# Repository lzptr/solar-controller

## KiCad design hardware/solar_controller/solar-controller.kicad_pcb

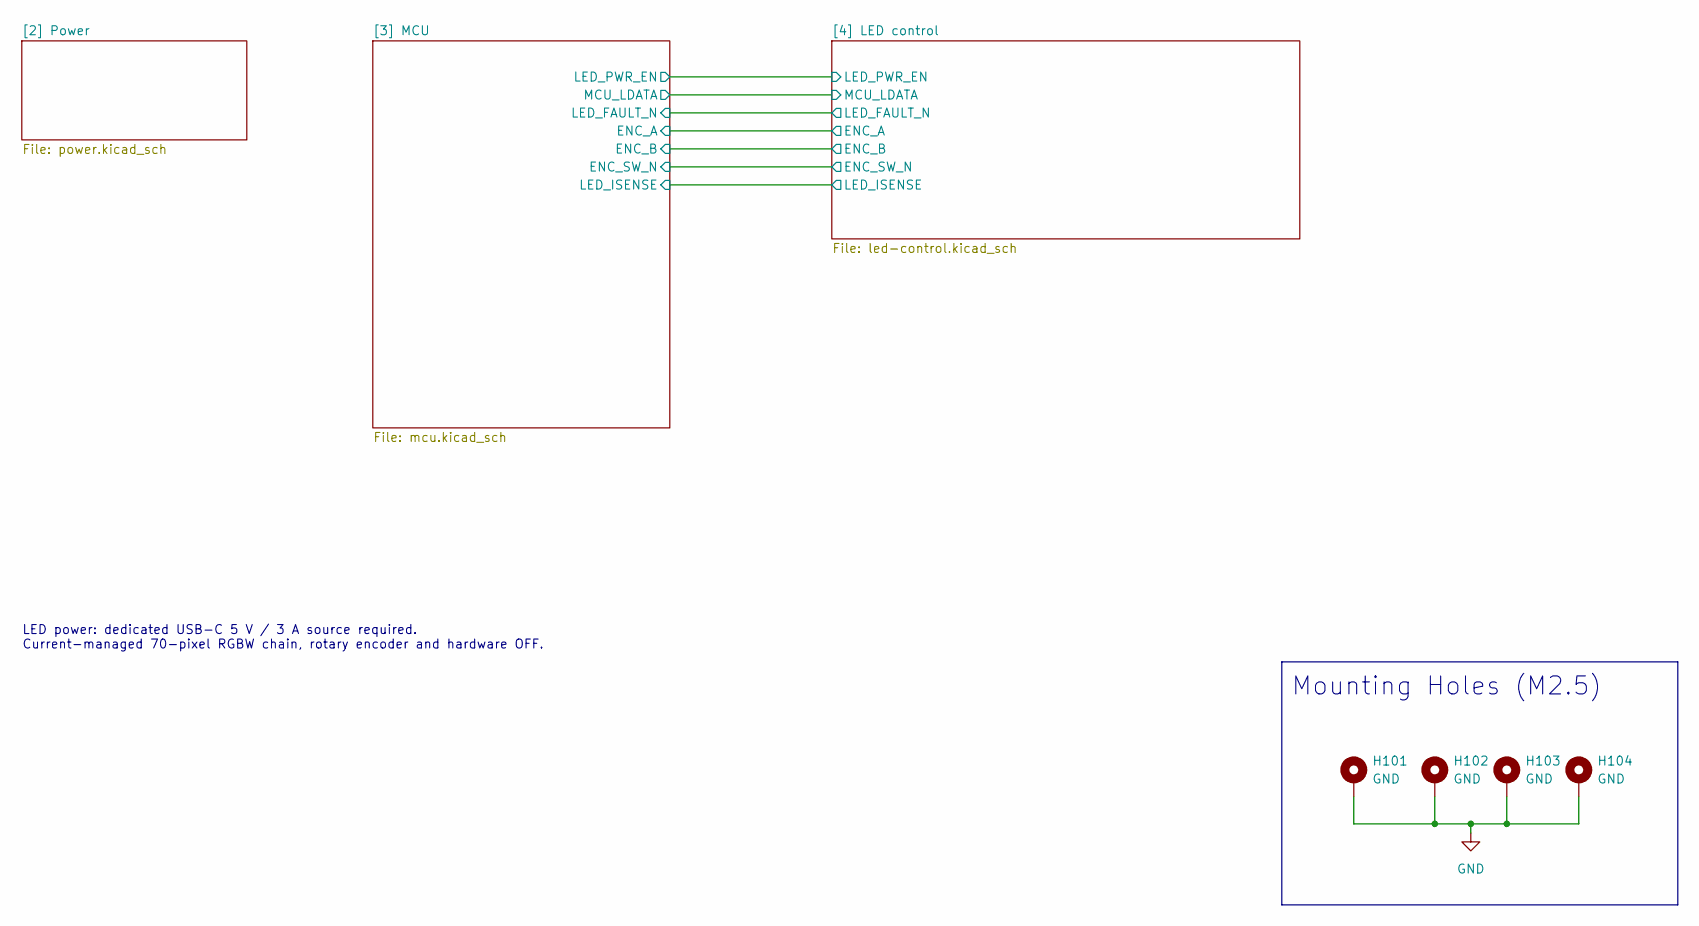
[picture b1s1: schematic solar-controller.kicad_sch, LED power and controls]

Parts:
H101, H102, H103, H104: GND; MountingHole_2.7mm_M2.5_ISO14580_Pad

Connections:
GND: H101.1 (1_1), H102.1 (1_1), H103.1 (1_1), H104.1 (1_1); also elsewhere on the board

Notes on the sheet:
Mounting Holes (M2.5)
LED power: dedicated USB-C 5 V / 3 A source required. Current-managed 70-pixel RGBW chain, rotary encoder and hardware OFF.

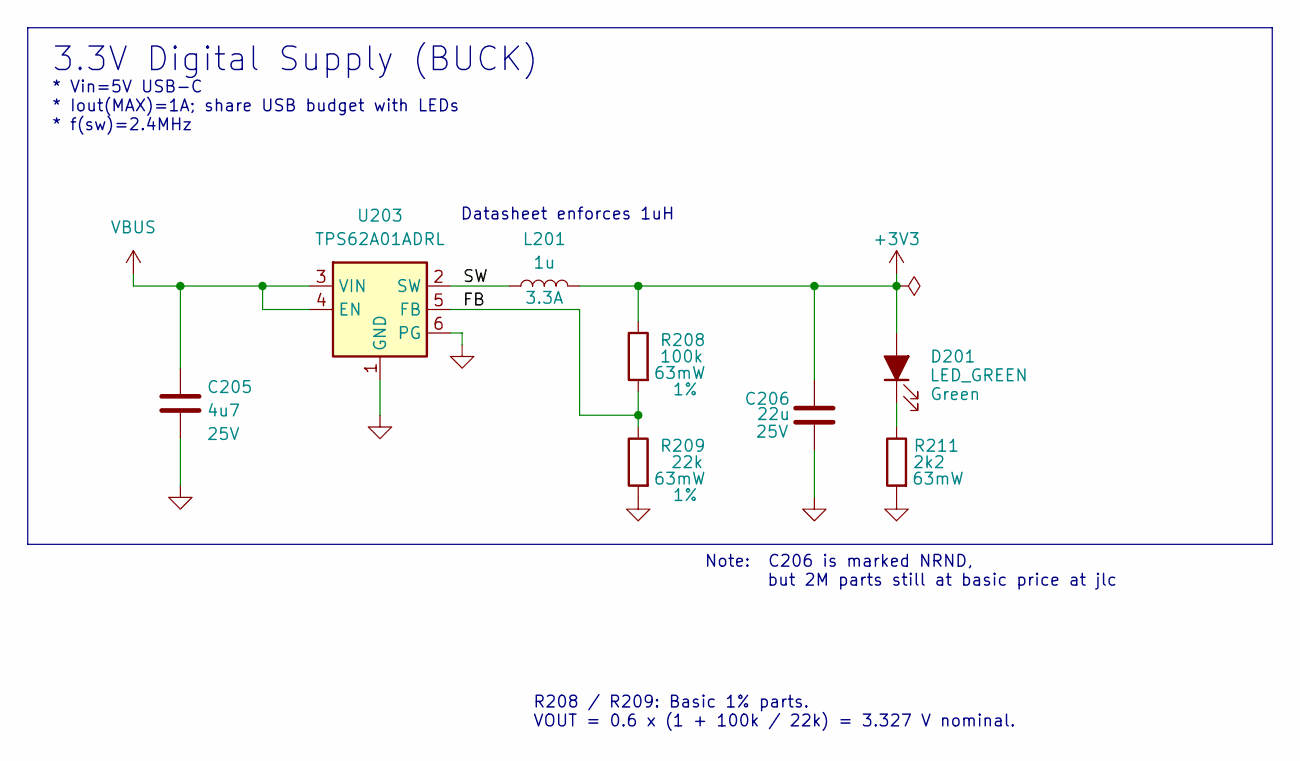
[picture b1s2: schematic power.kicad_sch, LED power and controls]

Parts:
C205: 4u7; C_0805_2012Metric; Rating 25V; LCSC Part # C1779
C206: 22u; C_0805_2012Metric; Rating 25V; LCSC Part # C45783
D201: LED_GREEN; LED_0603_1608Metric; Rating Green; LCSC Part # C965804
L201: 1u; L_1008_2520Metric; Rating 3.3A; LCSC Part # C435392
R208: 100k; R_0402_1005Metric; Rating 63mW; LCSC Part # C25741
R209: 22k; R_0402_1005Metric; Rating 63mW; LCSC Part # C25768
R211: 2k2; R_0402_1005Metric; Rating 63mW; LCSC Part # C25879
U203: TPS62A01ADRL; SOT-563; LCSC Part # C5181455

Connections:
+3V3: C206.1, D201.2 (A), L201.2, R208.1; also elsewhere on the board
/[2] Power/FB: R208.2, R209.1, U203.5 (FB)
/[2] Power/SW: L201.1, U203.2 (SW)
GND: C205.2, C206.2, R209.2, R211.2, U203.1 (GND), U203.6 (PG); also elsewhere on the board
unnamed: D201.1 (K), R211.1
VBUS: C205.1, U203.3 (VIN), U203.4 (EN); also elsewhere on the board

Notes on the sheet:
* Vin=5V USB-C * Iout(MAX)=1A; share USB budget with LEDs * f(sw)=2.4MHz
Datasheet enforces 1uH
Note: C206 is marked NRND, but 2M parts still at basic price at jlc
3.3V Digital Supply (BUCK)
R208 / R209: Basic 1% parts. VOUT = 0.6 x (1 + 100k / 22k) = 3.327 V nominal.

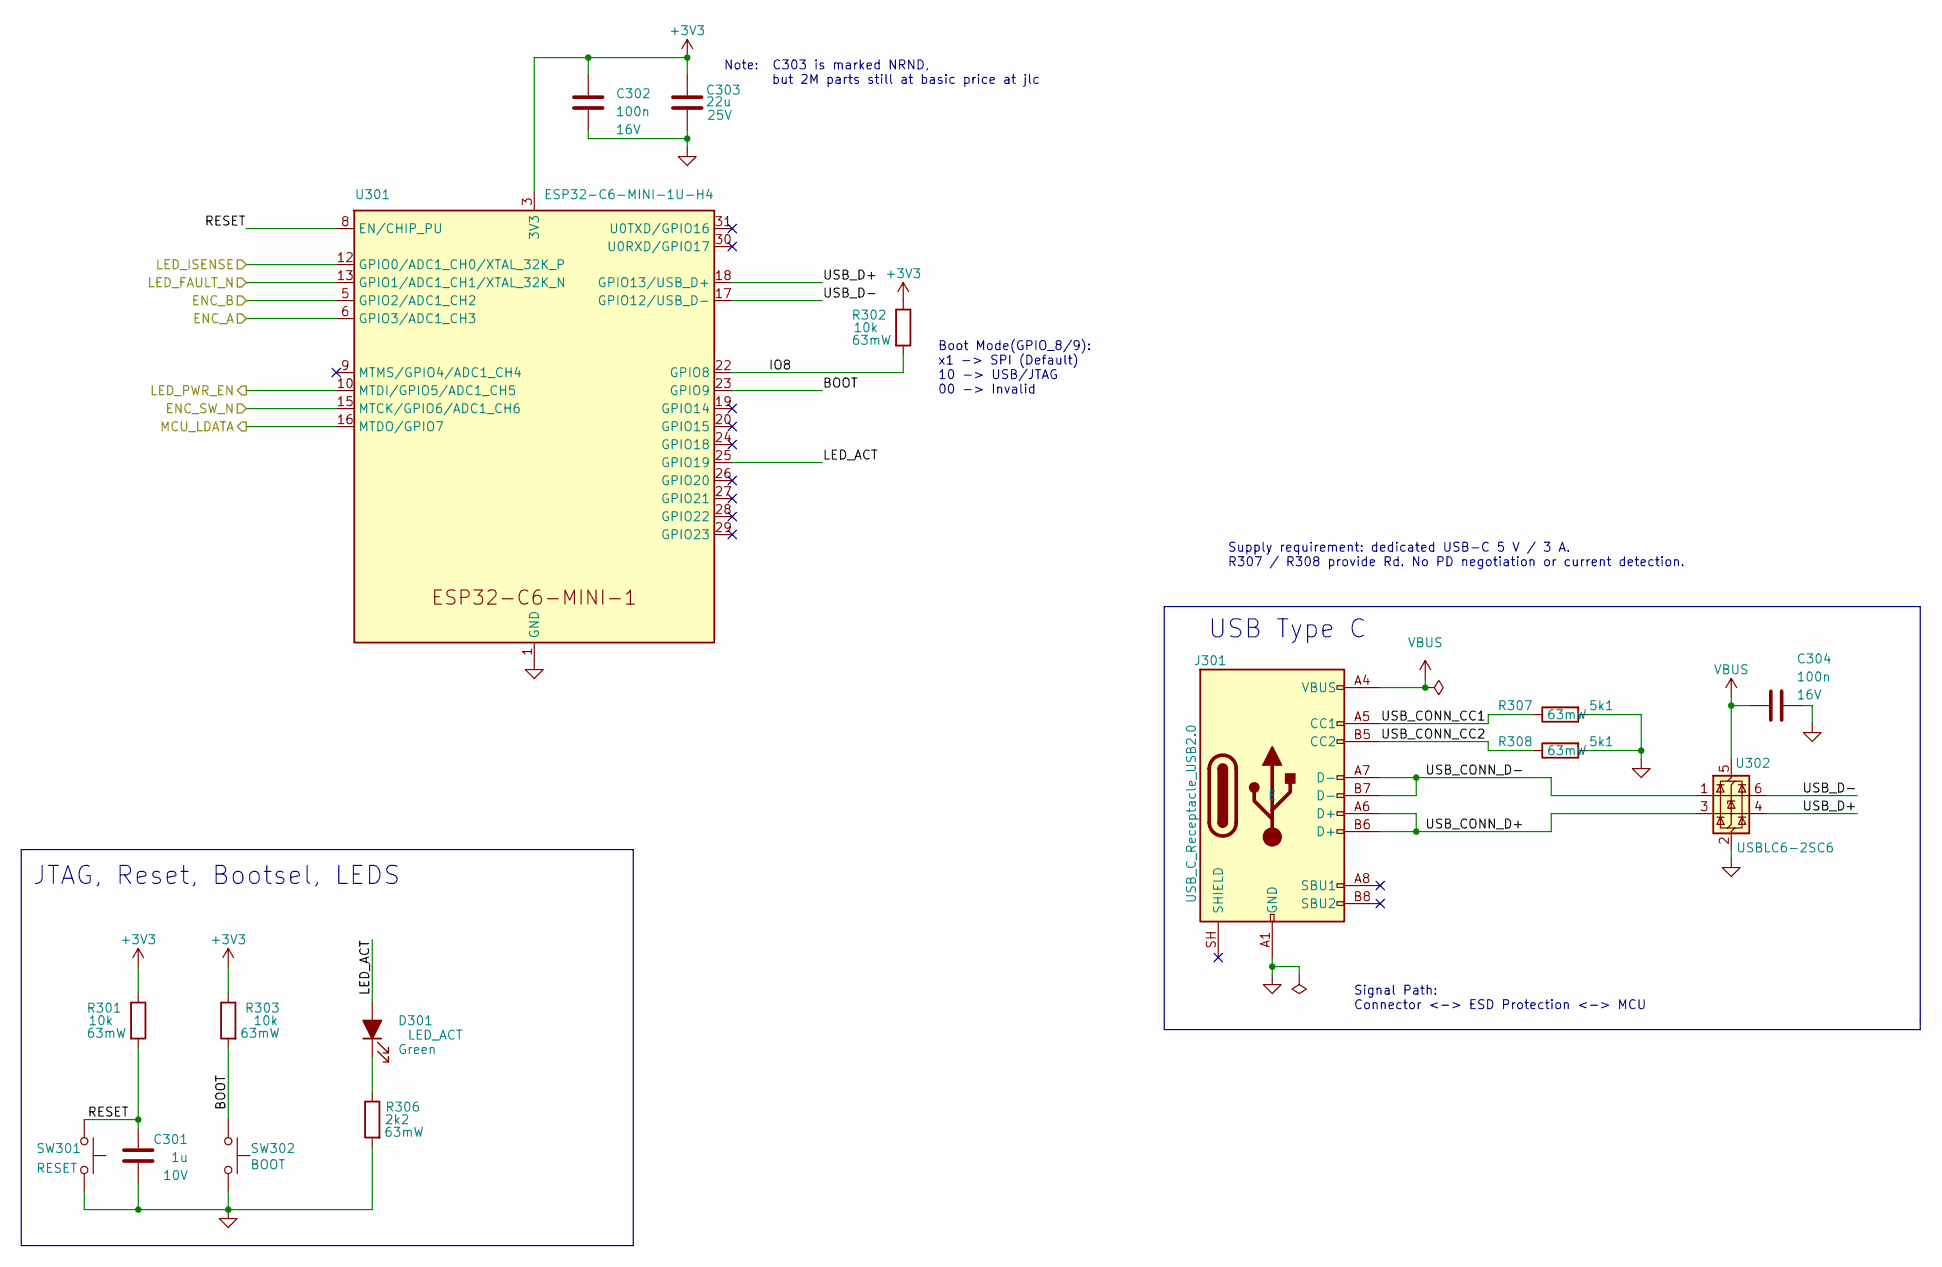
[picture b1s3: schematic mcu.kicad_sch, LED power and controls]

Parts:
C301: 1u; C_0402_1005Metric; Rating 10V; LCSC Part # C14445
C302, C304: 100n; C_0402_1005Metric; Rating 16V; LCSC Part # C1525
C303: 22u; C_0805_2012Metric; Rating 25V; LCSC Part # C45783
D301: LED_ACT; LED_0603_1608Metric; Rating Green; LCSC Part # C965804
J301: USB_C_Receptacle_USB2.0; USB_C_Receptacle_HRO_TYPE-C-31-M-12; LCSC Part # C165948
R301, R302, R303: 10k; R_0402_1005Metric; Rating 63mW; LCSC Part # C25744
R306: 2k2; R_0402_1005Metric; Rating 63mW; LCSC Part # C25879
R307, R308: 5k1; R_0402_1005Metric; Rating 63mW; LCSC Part # C25905
SW301: RESET; SW_SPST_TS-1088-xR020; LCSC Part # C720477
SW302: BOOT; SW_SPST_TS-1088-xR020; LCSC Part # C720477
U301: ESP32-C6-MINI-1U-H4; ESP32-C6-MINI-1U; LCSC Part # C20627095
U302: USBLC6-2SC6; SOT-23-6; LCSC Part # C5261088

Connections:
+3V3: C302.1, C303.1, R301.1, R302.1, R303.1, U301.3 (3V3); also elsewhere on the board
/[3] MCU/BOOT: R303.2, SW302.1, U301.23 (GPIO9)
/[3] MCU/ENC_A: U301.6 (GPIO3/ADC1_CH3); also elsewhere on the board
/[3] MCU/ENC_B: U301.5 (GPIO2/ADC1_CH2); also elsewhere on the board
/[3] MCU/ENC_SW_N: U301.15 (MTCK/GPIO6/ADC1_CH6); also elsewhere on the board
/[3] MCU/IO8: R302.2, U301.22 (GPIO8)
/[3] MCU/LED_ACT: D301.2 (A), U301.25 (GPIO19)
/[3] MCU/LED_FAULT_N: U301.13 (GPIO1/ADC1_CH1/XTAL_32K_N); also elsewhere on the board
/[3] MCU/LED_ISENSE: U301.12 (GPIO0/ADC1_CH0/XTAL_32K_P); also elsewhere on the board
/[3] MCU/LED_PWR_EN: U301.10 (MTDI/GPIO5/ADC1_CH5); also elsewhere on the board
/[3] MCU/MCU_LDATA: U301.16 (MTDO/GPIO7); also elsewhere on the board
/[3] MCU/RESET: C301.1, R301.2, SW301.1, U301.8 (EN/CHIP_PU)
/[3] MCU/USB_CONN_CC1: J301.A5 (CC1), R307.1
/[3] MCU/USB_CONN_CC2: J301.B5 (CC2), R308.1
/[3] MCU/USB_CONN_D+: J301.A6 (D+), J301.B6 (D+), U302.3 (I/O2)
/[3] MCU/USB_CONN_D-: J301.A7 (D-), J301.B7 (D-), U302.1 (I/O1)
/[3] MCU/USB_D+: U301.18 (GPIO13/USB_D+), U302.4 (I/O2)
/[3] MCU/USB_D-: U301.17 (GPIO12/USB_D-), U302.6 (I/O1)
GND: C301.2, C302.2, C303.2, C304.2, J301.A1 (GND), J301.A12 (GND), J301.B1 (GND), J301.B12 (GND), R306.2, R307.2, R308.2, SW301.2, SW302.2, U301.1 (GND), U301.2 (GND), U301.11 (GND), U301.14 (GND), U301.36 (GND), U301.37 (GND), U301.38 (GND), U301.39 (GND), U301.40 (GND), U301.41 (GND), U301.42 (GND), U301.43 (GND), U301.44 (GND), U301.45 (GND), U301.46 (GND), U301.47 (GND), U301.48 (GND), U301.49 (GND), U301.50 (GND), U301.51 (GND), U301.52 (GND), U301.53 (GND), U302.2 (GND); also elsewhere on the board
unnamed: D301.1 (K), R306.1
VBUS: C304.1, J301.A4 (VBUS), J301.A9 (VBUS), J301.B4 (VBUS), J301.B9 (VBUS), U302.5 (VBUS); also elsewhere on the board

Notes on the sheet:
Signal Path: Connector <-> ESD Protection <-> MCU
Note: C303 is marked NRND, but 2M parts still at basic price at jlc
Boot Mode(GPIO_8/9): x1 -> SPI (Default) 10 -> USB/JTAG 00 -> Invalid
USB Type C
Supply requirement: dedicated USB-C 5 V / 3 A. R307 / R308 provide Rd. No PD negotiation or current detection.
JTAG, Reset, Bootsel, LEDS

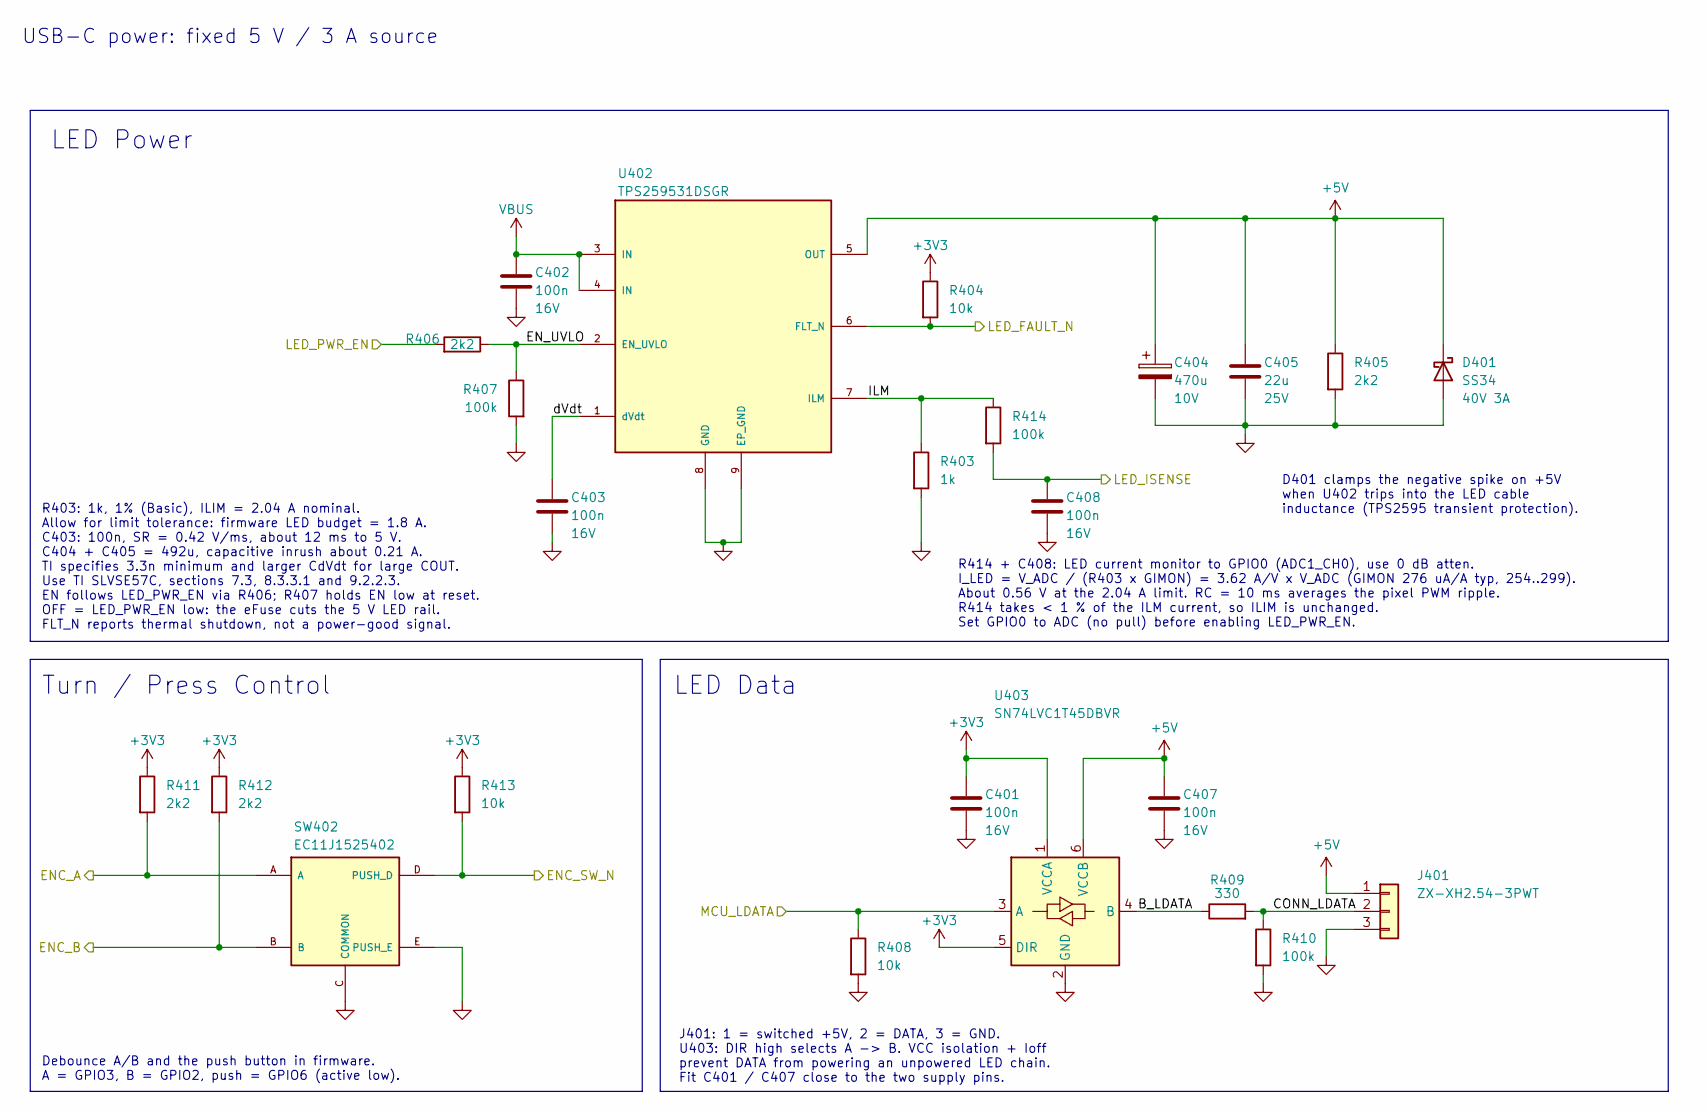
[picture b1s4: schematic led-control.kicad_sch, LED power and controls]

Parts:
C401, C402, C403, C407, C408: 100n; C_0402_1005Metric; Rating 16V; LCSC Part # C1525
C404: 470u; CP_Elec_6.3x7.7; Rating 10V; MPN MA10V470M6X8; LCSC Part # C46550459
C405: 22u; C_0805_2012Metric; Rating 25V; LCSC Part # C45783
D401: SS34; D_SMA; Rating 40V 3A; MPN SS34; LCSC Part # C8678
J401: ZX-XH2.54-3PWT; Megastar_ZX-XH2.54-3PWT; Rating 3A / contact; MPN ZX-XH2.54-3PWT; LCSC Part # C7429672
R403: 1k; R_0402_1005Metric; Rating 62.5mW; MPN 0402WGF1001TCE; LCSC Part # C11702
R404, R408, R413: 10k; R_0402_1005Metric; Rating 63mW; LCSC Part # C25744
R405, R406, R411, R412: 2k2; R_0402_1005Metric; Rating 63mW; LCSC Part # C25879
R407, R410, R414: 100k; R_0402_1005Metric; Rating 63mW; LCSC Part # C25741
R409: 330; R_0402_1005Metric; Rating 63mW; LCSC Part # C25104
SW402: EC11J1525402; ALPS_EC11J1525402; Rating 10mA / 5V; LCSC Part # C209762
U402: TPS259531DSGR; Texas_DSG0008A_WSON-8-1EP_2x2mm_P0.5mm_EP0.9x1.6mm; Rating 5V branch / 2.04A nominal; LCSC Part # C2155674
U403: SN74LVC1T45DBVR; SOT-23-6; Rating 3.3V -> switched 5V; LCSC Part # C7843

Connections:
+3V3: C401.1, R404.1, R411.1, R412.1, R413.1, U403.1 (VCCA), U403.5 (DIR); also elsewhere on the board
+5V: C404.1, C405.1, C407.1, D401.1 (K), J401.1, R405.1, U402.5 (OUT), U403.6 (VCCB)
/[3] MCU/ENC_A: R411.2, SW402.A; also elsewhere on the board
/[3] MCU/ENC_B: R412.2, SW402.B; also elsewhere on the board
/[3] MCU/ENC_SW_N: R413.2, SW402.D (PUSH_D); also elsewhere on the board
/[3] MCU/LED_FAULT_N: R404.2, U402.6 (FLT_N); also elsewhere on the board
/[3] MCU/LED_ISENSE: C408.1, R414.2; also elsewhere on the board
/[3] MCU/LED_PWR_EN: R406.2; also elsewhere on the board
/[3] MCU/MCU_LDATA: R408.1, U403.3 (A); also elsewhere on the board
/[4] LED control/B_LDATA: R409.1, U403.4 (B)
/[4] LED control/CONN_LDATA: J401.2, R409.2, R410.1
/[4] LED control/EN_UVLO: R406.1, R407.1, U402.2 (EN_UVLO)
/[4] LED control/ILM: R403.1, R414.1, U402.7 (ILM)
/[4] LED control/dVdt: C403.1, U402.1 (dVdt)
GND: C401.2, C402.2, C403.2, C404.2, C405.2, C407.2, C408.2, D401.2 (A), J401.3, R403.2, R405.2, R407.2, R408.2, R410.2, SW402.C (COMMON), SW402.E (PUSH_E), U402.8 (GND), U402.9 (EP_GND), U403.2 (GND); also elsewhere on the board
VBUS: C402.1, U402.3 (IN), U402.4 (IN); also elsewhere on the board

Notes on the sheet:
USB-C power: fixed 5 V / 3 A source
LED Data
R403: 1k, 1% (Basic), ILIM = 2.04 A nominal. Allow for limit tolerance: firmware LED budget = 1.8 A. C403: 100n, SR = 0.42 V/ms, about 12 ms to 5 V. C404 + C405 = 492u, capacitive inrush about 0.21 A. TI specifies 3.3n minimum and larger CdVdt for large COUT. Use TI SLVSE57C, sections 7.3, 8.3.3.1 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
LED Power
J401: 1 = switched +5V, 2 = DATA, 3 = GND. U403: DIR high selects A -> B. VCC isolation + Ioff prevent DATA from powering an unpowered LED chain. Fit C401 / C407 close to the two supply pins.
Turn / Press Control
R414 + C408: LED current monitor to GPIO0 (ADC1_CH0), use 0 dB atten. I_LED = V_ADC / (R403 x GIMON) = 3.62 A/V x V_ADC (GIMON 276 uA/A typ, 254..299). About 0.56 V at the 2.04 A limit. RC = 10 ms averages the pixel PWM ripple. R414 takes < 1 % of the ILM current, so ILIM is unchanged. Set GPIO0 to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
D401 clamps the negative spike on +5V when U402 trips into the LED cable inductance (TPS2595 transient protection).
Debounce A/B and the push button in firmware. A = GPIO3, B = GPIO2, push = GPIO6 (active low).

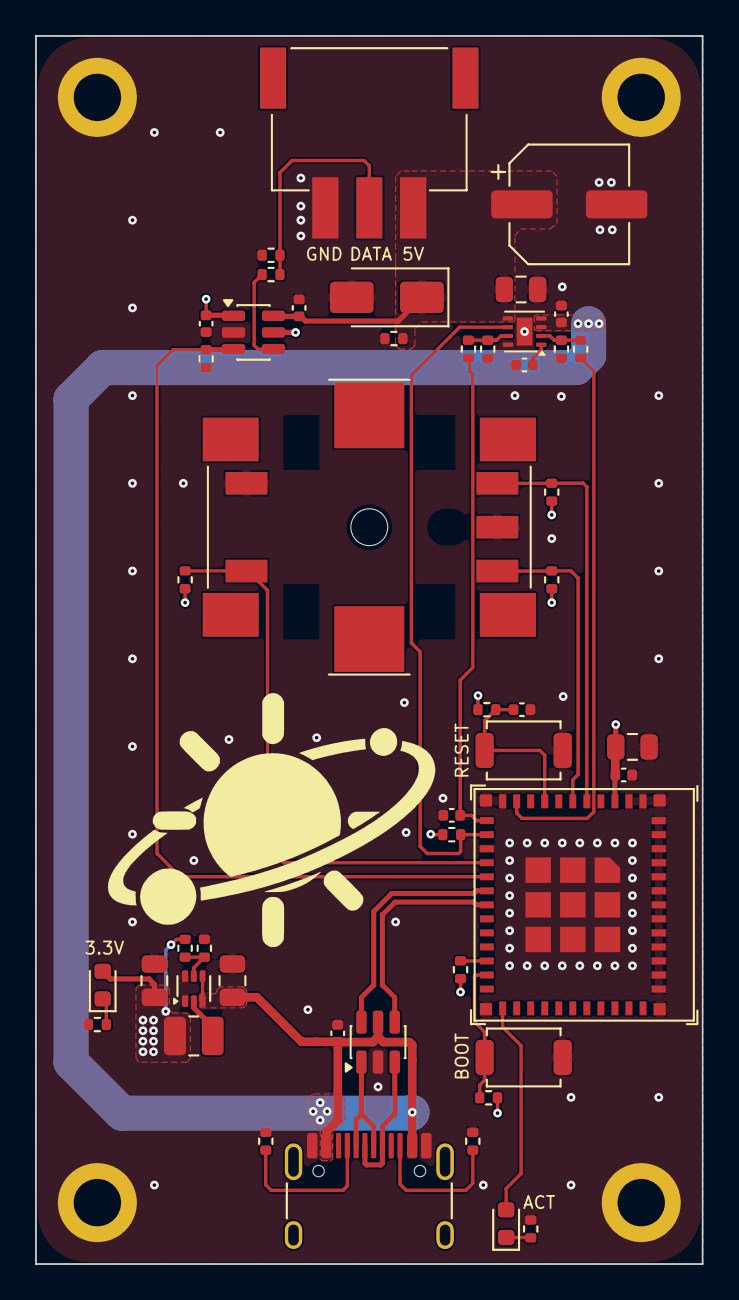
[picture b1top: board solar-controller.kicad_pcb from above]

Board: 4 copper layers, 38.0 x 70.0 mm, 52 parts (0 on the bottom side), 30 nets.

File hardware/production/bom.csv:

Designator,Footprint,Quantity,Value,LCSC Part #
C205,0805,1,4u7,C1779
"C206, C303, C405",0805,3,22u,C45783
C301,0402,1,1u,C14445
"C302, C304, C401, C402, C403, C407, C408",0402,7,100n,C1525
C404,CP_Elec_6.3x7.7,1,470u,C46550459
D201,0603,1,LED_GREEN,C965804
D301,0603,1,LED_ACT,C965804
D401,D_SMA,1,SS34,C8678
J301,USB_C_Receptacle_HRO_TYPE-C-31-M-12,1,USB_C_Receptacle_USB2.0,C165948
J401,Megastar_ZX-XH2.54-3PWT,1,ZX-XH2.54-3PWT,C7429672
L201,1008,1,1u,C435392
"R208, R407, R410, R414",0402,4,100k,C25741
R209,0402,1,22k,C25768
"R211, R306, R405, R406, R411, R412",0402,6,2k2,C25879
"R301, R302, R303, R404, R408, R413",0402,6,10k,C25744
"R307, R308",0402,2,5k1,C25905
R403,0402,1,1k,C11702
R409,0402,1,330,C25104
SW301,SW_SPST_TS-1088-xR020,1,RESET,C720477
SW302,SW_SPST_TS-1088-xR020,1,BOOT,C720477
SW402,ALPS_EC11J1525402,1,EC11J1525402,C209762
U203,SOT-563,1,TPS62A01ADRL,C5181455
U301,ESP32-C6-MINI-1U,1,ESP32-C6-MINI-1U-H4,C20627095
U302,SOT-23-6,1,USBLC6-2SC6,C5261088
U402,Texas_DSG0008A_WSON-8-1EP_2x2mm_P0.5mm_EP0.9x1.6mm,1,TPS259531DSGR,C2155674
U403,SOT-23-6,1,SN74LVC1T45DBVR,C7843

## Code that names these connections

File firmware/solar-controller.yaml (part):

# Solar controller rev 0.1: ESP32-C6-MINI-1U-H4 driving a chain of 10 lithophane
# globes (Sun + 9 planets, 7 SK6812 RGBW LEDs each) through a TPS259531 eFuse.
#
#   GPIO0  ILM   eFuse current monitor, 276 mV/A (ADC1_CH0)
#   GPIO1  FLT   eFuse fault, open drain, low on thermal shutdown (R404 pull-up)
#   GPIO2  ENC_B encoder B (2k2 pull-up)
#   GPIO3  ENC_A encoder A (2k2 pull-up)
#   GPIO5  EN    eFuse enable, high = LED 5 V on
#   GPIO6  SW    encoder push, active low (10k pull-up)
#   GPIO7  DATA  SK6812 data through the SN74LVC1T45 on the switched 5 V
#   GPIO19 D301  status LED
#
# Build and flash from this folder: esphome run solar-controller.yaml

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
power_supply:
  - id: led_power
    pin: GPIO5
    # C403 ramps the 5 V at about 0.42 V/ms.
    enable_time: 50ms
    keep_on_time: 100ms
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output:
  - platform: gpio
    id: status_out
    pin: GPIO19

light:
  - platform: esp32_rmt_led_strip
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    output_id: strip
    name: None
    icon: mdi:orbit
    pin: GPIO7
    num_leds: ${led_count}
    chipset: SK6812
    is_rgbw: true
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sensor:
  - platform: adc
    id: ilm_voltage
    pin: GPIO0
    attenuation: 2.5db
    samples: 8
    update_interval: 100ms
    internal: true
  - platform: rotary_encoder
    id: knob
    pin_a: GPIO3
    pin_b: GPIO2
    # EC11J1525402: 15 pulses, 30 detents per turn, so one count per detent.
    resolution: 2
    internal: true
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    device_class: problem
    entity_category: diagnostic
    pin:
      number: GPIO1
      inverted: true
    on_press:
      # FLT only means something while the eFuse is enabled.
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  - platform: gpio
    id: knob_button
    pin:
      number: GPIO6
      inverted: true
    internal: true
    filters:
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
